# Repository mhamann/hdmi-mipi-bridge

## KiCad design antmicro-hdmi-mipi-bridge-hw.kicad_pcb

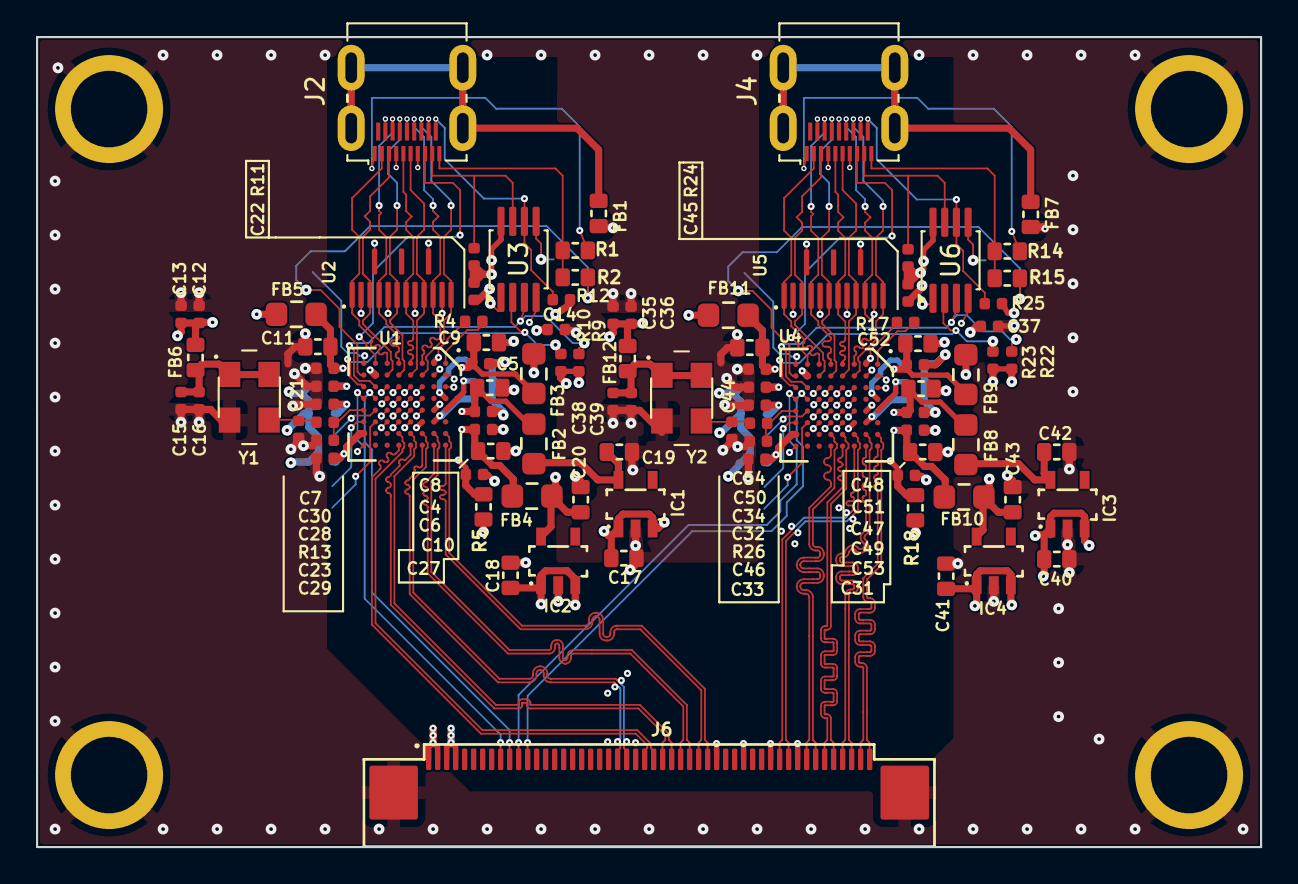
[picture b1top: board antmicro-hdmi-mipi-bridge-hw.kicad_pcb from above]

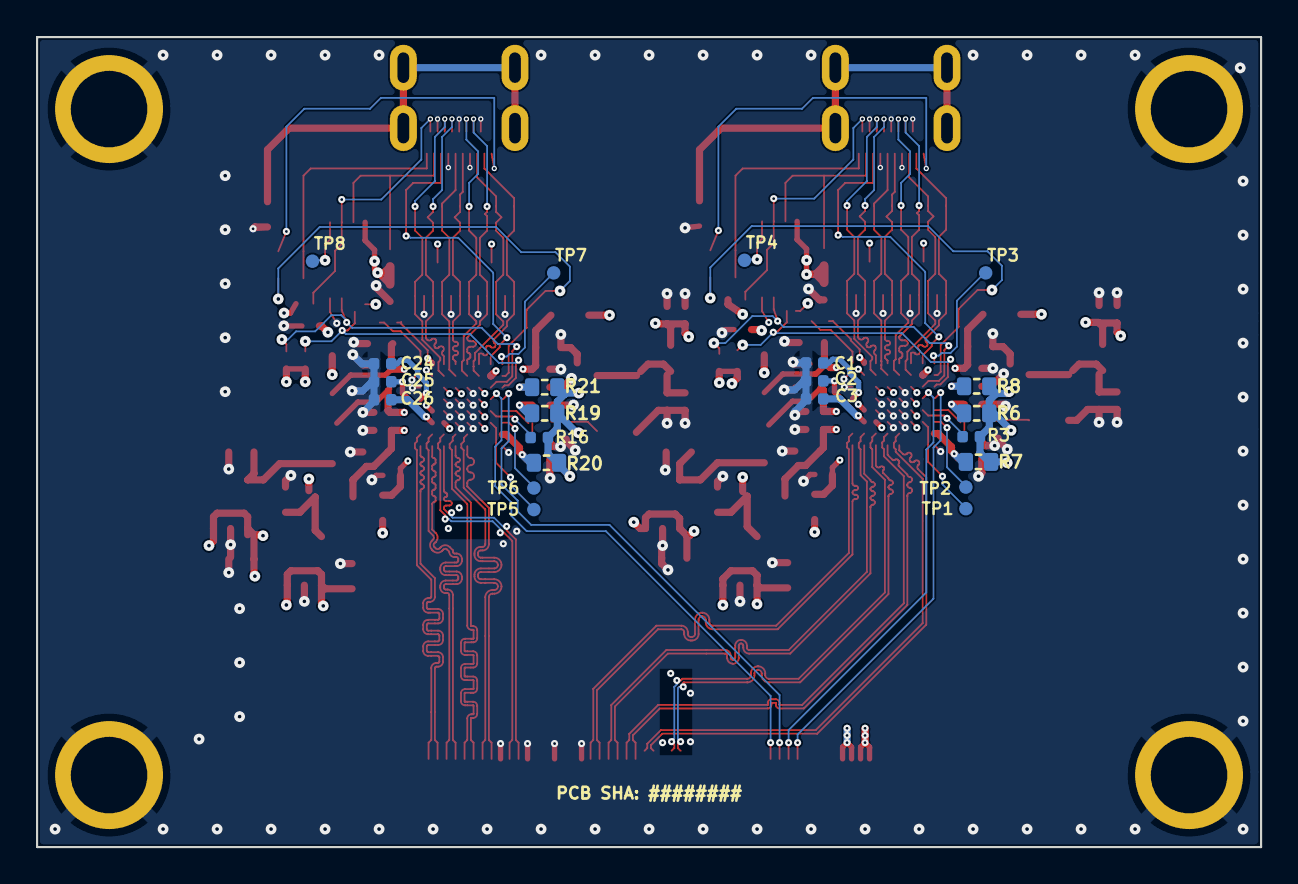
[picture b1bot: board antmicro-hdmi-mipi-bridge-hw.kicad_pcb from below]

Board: 4 copper layers, 68.0 x 45.0 mm, 121 parts (26 on the bottom side), 105 nets.

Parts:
C1, C2, C3, C12, C14, C15, C22, C24, C25, C26, C27, C28, C29, C30, C31, C32, C33, C34, C35, C37, C38, C45: C_100n_0402; C_0402_1005Metric
C4, C5, C6, C7, C47, C48, C49, C50: C_470p_0402; C_0402_1005Metric
C8, C9, C10, C11, C51, C52, C53, C54: C_4u7_0603; C_0603_1608Metric
C13, C16, C21, C23, C36, C39, C44, C46: C_47p_0402; C_0402_1005Metric
C17, C18, C19, C20, C40, C41, C42, C43: C_10u_0603; C_0603_1608Metric
FB1, FB7: FB_120Z_3A_Murata-BLM18SG_0603; FB_0603_1608Metric
FB2, FB3, FB4, FB5, FB8, FB9, FB10, FB11: FB_1kZ_0.8A_WE-CBF_0805; FB_0805_2012Metric
FB6, FB12: FB_600Z_0.5A_Murata-BLM18AG_0603; FB_0603_1608Metric
IC1, IC3: TLV73325PDBVR; SOT-23-5
IC2, IC4: TLV74312PDBVR; SOT-23-5
J2, J4: HDMI-D_Molex_467651001; HDMI_Micro-D_Molex_46765-1xxx
J6: Conn_FFC_WE_68715014022; Conn_FFC_WE_68715014x22
N1: antmicro_logo; antmicro-logo_scaled_20mm_mask
N2: oshw_logo; OSHW-Logo_7.5x8mm_Mask
R1, R2, R5, R6, R7, R8, R14, R15, R18, R19, R20, R21: R_0R_0603; R_0603_1608Metric
R3, R9, R10, R11, R12, R16, R22, R23, R24, R25: R_10k_0402; R_0402_1005Metric
R4, R17: R_2k_0402; R_0402_1005Metric
R13, R26: R_22R_0402; R_0402_1005Metric
SP1, SP2, SP3, SP4: Spacer_Drill4.25mm_H6mm_SMTSO2560CTJ
TP1, TP2, TP3, TP4, TP5, TP6, TP7, TP8: TP_0.75mm_SMD; TP_SMD_0.75mm
U1, U4: TC358743XBG; BGA-64_8x8_6.0x6.0mm
U2, U5: TPD8S009DSMR; R-PDSO-N15
U3, U6: PCA9517ADP; MSOP-8_3x3mm_P0.65mm
Y1, Y2: Oscillator_27MHz_HELE_SSI027000E3CH; Oscillator_SMD_TXC_7C_5x3.2x1.2mm

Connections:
+3V3: C12.2, C13.2, C14.1, C17.2, C18.2, C35.2, C36.2, C37.1, C40.2, C41.2, FB6.1, FB12.1, IC1.1 (VIN), IC1.3 (EN), IC2.1 (VIN), IC2.3 (EN), IC3.1 (VIN), IC3.3 (EN), IC4.1 (VIN), IC4.3 (EN), J6.3, J6.4, R3.2, R6.2, R7.2, R8.2, R9.2, R10.2, R16.2, R19.2, R20.2, R21.2, R22.2, R23.2, U2.13 (VCC), U2.15 (VCC), U3.1, U5.13 (VCC), U5.15 (VCC), U6.1
+5V: C22.2, C45.2, J6.1, J6.2, R11.2, R12.2, R24.2, R25.2, U3.8, U6.8
/Channel 1/CH1_AVDD33: C30.2, R4.2, R8.1, U1.B1 (AVDD33), U1.F3 (AVDD33)
/Channel 1/CH1_REFCLK: C23.2, R13.2, U1.H5 (REFCLK)
/Channel 1/CH1_~RST: R3.1, U1.G5 (~RESET)
/Channel 1/HDMI1_CEC: J2.15, U1.G1 (CEC)
/Channel 1/HDMI1_CLK_N: J2.14, U1.C2 (HDMIC_N), U2.12 (D3-)
/Channel 1/HDMI1_CLK_P: J2.12, U1.C1 (HDMIC_P), U2.10 (D3+)
/Channel 1/HDMI1_D0_N: J2.11, U1.D2 (HDMID0_N), U2.9 (D2-)
/Channel 1/HDMI1_D0_P: J2.9, U1.D1 (HDMID0_P), U2.7 (D2+)
/Channel 1/HDMI1_D1_N: J2.8, U1.E2 (HDMID1_N), U2.6 (D1-)
/Channel 1/HDMI1_D1_P: J2.6, U1.E1 (HDMID1_P), U2.4 (D1+)
/Channel 1/HDMI1_D2_N: J2.5, U1.F2 (HDMID2_N), U2.3 (D0-)
/Channel 1/HDMI1_D2_P: J2.3, U1.F1 (HDMID2_P), U2.1 (D0+)
/Channel 1/HDMI1_DDC_SCL: J2.17, R11.1, U3.7
/Channel 1/HDMI1_DDC_SCL_3V3: R10.1, U1.H3 (DDC_SCL), U3.2
/Channel 1/HDMI1_DDC_SDA: J2.18, R12.1, U3.6
/Channel 1/HDMI1_DDC_SDA_3V3: R9.1, U1.G3 (DDC_SDA), U3.3
/Channel 1/HDMI1_HPD: J2.1, R1.2
/Channel 1/HDMI1_HPDI: R2.2, U1.H2 (HPDI)
/Channel 1/HDMI1_HPDO: TP3.1, U1.H1 (HPDO)
/Channel 1/HDMI1_POWER: J2.19, R1.1, R2.1
/Channel 2/CH2_AVDD33: C34.2, R17.2, R21.1, U4.B1 (AVDD33), U4.F3 (AVDD33)
/Channel 2/CH2_REFCLK: C46.2, R26.2, U4.H5 (REFCLK)
/Channel 2/CH2_~RST: R16.1, U4.G5 (~RESET)
/Channel 2/HDMI2_CEC: J4.15, U4.G1 (CEC)
/Channel 2/HDMI2_CLK_N: J4.14, U4.C2 (HDMIC_N), U5.12 (D3-)
/Channel 2/HDMI2_CLK_P: J4.12, U4.C1 (HDMIC_P), U5.10 (D3+)
/Channel 2/HDMI2_D0_N: J4.11, U4.D2 (HDMID0_N), U5.9 (D2-)
/Channel 2/HDMI2_D0_P: J4.9, U4.D1 (HDMID0_P), U5.7 (D2+)
/Channel 2/HDMI2_D1_N: J4.8, U4.E2 (HDMID1_N), U5.6 (D1-)
/Channel 2/HDMI2_D1_P: J4.6, U4.E1 (HDMID1_P), U5.4 (D1+)
/Channel 2/HDMI2_D2_N: J4.5, U4.F2 (HDMID2_N), U5.3 (D0-)
/Channel 2/HDMI2_D2_P: J4.3, U4.F1 (HDMID2_P), U5.1 (D0+)
/Channel 2/HDMI2_DDC_SCL: J4.17, R24.1, U6.7
/Channel 2/HDMI2_DDC_SCL_3V3: R23.1, U4.H3 (DDC_SCL), U6.2
/Channel 2/HDMI2_DDC_SDA: J4.18, R25.1, U6.6
/Channel 2/HDMI2_DDC_SDA_3V3: R22.1, U4.G3 (DDC_SDA), U6.3
/Channel 2/HDMI2_HPD: J4.1, R14.2
/Channel 2/HDMI2_HPDI: R15.2, U4.H2 (HPDI)
/Channel 2/HDMI2_HPDO: TP7.1, U4.H1 (HPDO)
/Channel 2/HDMI2_POWER: J4.19, R14.1, R15.1
CH1_1V2: C20.2, FB3.2, FB4.2, FB5.2, IC2.5 (VOUT)
CH1_2V5: C19.2, FB2.2, IC1.5 (VOUT)
CH2_1V2: C43.2, FB9.2, FB10.2, FB11.2, IC4.5 (VOUT)
CH2_2V5: C42.2, FB8.2, IC3.5 (VOUT)
CSI1_CLK_N: J6.23, U1.C7 (CSIC_N)
CSI1_CLK_P: J6.22, U1.C8 (CSIC_P)
CSI1_D1_N: J6.26, U1.E7 (CSID0_N)
CSI1_D1_P: J6.25, U1.E8 (CSID0_P)
CSI1_D2_N: J6.28, U1.D7 (CSID1_N)
CSI1_D2_P: J6.27, U1.D8 (CSID1_P)
CSI1_D3_N: J6.30, U1.B7 (CSID2_N)
CSI1_D3_P: J6.29, U1.B8 (CSID2_P)
CSI1_D4_N: J6.32, U1.A7 (CSID3_N)
CSI1_D4_P: J6.31, U1.A8 (CSID3_P)
CSI3_CLK_N: J6.41, U4.C7 (CSIC_N)
CSI3_CLK_P: J6.40, U4.C8 (CSIC_P)
CSI3_D1_N: J6.44, U4.E7 (CSID0_N)
CSI3_D1_P: J6.43, U4.E8 (CSID0_P)
CSI3_D2_N: J6.46, U4.D7 (CSID1_N)
CSI3_D2_P: J6.45, U4.D8 (CSID1_P)
CSI3_D3_N: J6.48, U4.B7 (CSID2_N)
CSI3_D3_P: J6.47, U4.B8 (CSID2_P)
CSI3_D4_N: J6.50, U4.A7 (CSID3_N)
CSI3_D4_P: J6.49, U4.A8 (CSID3_P)
GND: C1.1, C2.1, C3.1, C4.2, C5.2, C6.2, C7.2, C8.1, C9.1, C10.1, C11.1, C12.1, C13.1, C14.2, C15.1, C16.1, C17.1, C18.1, C19.1, C20.1, C21.1, C22.1, C23.1, C24.1, C25.1, C26.1, C27.1, C28.1, C29.1, C30.1, C31.1, C32.1, C33.1, C34.1, C35.1, C36.1, C37.2, C38.1, C39.1, C40.1, C41.1, C42.1, C43.1, C44.1, C45.1, C46.1, C47.2, C48.2, C49.2, C50.2, C51.1, C52.1, C53.1, C54.1, FB1.1, FB7.1, IC1.2 (GND), IC2.2 (GND), IC3.2 (GND), IC4.2 (GND), J2.4, J2.7, J2.10, J2.13, J2.16, J4.4, J4.7, J4.10, J4.13, J4.16, J6.33, J6.36, J6.39, J6.42, J6.MP1 (MP), J6.MP2 (MP), SP1.1, SP2.1, SP3.1, SP4.1, U1.A2 (GND), U1.A3 (VPGM), U1.C4 (GND), U1.C5 (GND), U1.D4 (GND), U1.D5 (GND), U1.D6 (GND), U1.E3 (GND), U1.E4 (GND), U1.E5 (TEST), U1.E6 (GND), U1.H8 (GND), U2.2 (GND), U2.5 (GND), U2.8 (GND), U2.11 (GND), U3.4, U4.A2 (GND), U4.A3 (VPGM), U4.C4 (GND), U4.C5 (GND), U4.D4 (GND), U4.D5 (GND), U4.D6 (GND), U4.E3 (GND), U4.E4 (GND), U4.E5 (TEST), U4.E6 (GND), U4.H8 (GND), U5.2 (GND), U5.5 (GND), U5.8 (GND), U5.11 (GND), U6.4, Y1.2 (GND), Y2.2 (GND)
I2C1_SCL: J6.9, U1.H4 (I2C_SCL)
I2C1_SDA: J6.10, U1.G4 (I2C_SDA)
I2C3_SCL: J6.11, U4.H4 (I2C_SCL)
I2C3_SDA: J6.12, U4.G4 (I2C_SDA)
unnamed: C5.1, C9.2, FB3.1, U1.B2 (AVDD12), U1.D3 (AVDD12)
unnamed: C6.1, C10.2, FB4.1, U1.C6 (VDD_MIPI), U1.F6 (VDD_MIPI)
unnamed: C27.2, R5.1, U1.C3 (VDDC2), U1.F5 (VDDC2)
unnamed: C31.2, R18.1, U4.C3 (VDDC2), U4.F5 (VDDC2)
unnamed: C48.1, C52.2, FB9.1, U4.B2 (AVDD12), U4.D3 (AVDD12)
unnamed: C49.1, C53.2, FB10.1, U4.C6 (VDD_MIPI), U4.F6 (VDD_MIPI)
unnamed: FB1.2, J2.SH
unnamed: FB7.2, J4.SH
unnamed: TP2.1, U1.H6 (EDID_SCL)
unnamed: TP1.1, U1.G6 (EDID_SDA)
unnamed: C4.1, C8.2, FB2.1, U1.B5 (AVDD25)
unnamed: R4.1, U1.A1 (REXT)
unnamed: C7.1, C11.2, FB5.1, R5.2, U1.G2 (VDDC1)
unnamed: C28.2, R6.1, U1.F4 (VDDIO1)
unnamed: C29.2, R7.1, U1.H7 (VDDIO2)
unnamed: C1.2, U1.A4 (BIASDA)
unnamed: C2.2, U1.A5 (DAOUT)
unnamed: C3.2, U1.B6 (PCKIN)
unnamed: TP4.1, U3.5
unnamed: TP6.1, U4.H6 (EDID_SCL)
unnamed: TP5.1, U4.G6 (EDID_SDA)
unnamed: C47.1, C51.2, FB8.1, U4.B5 (AVDD25)
unnamed: R17.1, U4.A1 (REXT)
unnamed: C50.1, C54.2, FB11.1, R18.2, U4.G2 (VDDC1)
unnamed: C32.2, R19.1, U4.F4 (VDDIO1)
unnamed: C33.2, R20.1, U4.H7 (VDDIO2)
unnamed: C24.2, U4.A4 (BIASDA)
unnamed: C25.2, U4.A5 (DAOUT)
unnamed: C26.2, U4.B6 (PCKIN)
unnamed: TP8.1, U6.5
unnamed: C15.2, C16.2, FB6.2, Y1.1 (EN), Y1.4 (VDD)
unnamed: C21.2, R13.1, Y1.3 (OUT)
unnamed: C38.2, C39.2, FB12.2, Y2.1 (EN), Y2.4 (VDD)
unnamed: C44.2, R26.1, Y2.3 (OUT)

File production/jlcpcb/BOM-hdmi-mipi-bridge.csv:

"Comment","Designator","Footprint","LCSC Part #","Qty","Manufacturer","MPN","Ordered part","Notes"
"C_100n_0402","C1,C2,C3,C12,C14,C15,C22,C24,C25,C26,C27,C28,C29,C30,C31,C32,C33,C34,C35,C37,C38,C45","C_0402_1005Metric","C85960","22","Murata","GRM155R61H104KE14D","Murata GRM155R61H104KE14D",""
"C_470p_0402","C4,C5,C6,C7,C47,C48,C49,C50","C_0402_1005Metric","C106207","8","Yageo","CC0402KRX7R9BB471","Yageo CC0402KRX7R9BB471","changed from Walsin 0402B471K250CT (out of stock)"
"C_4u7_0603","C8,C9,C10,C11,C51,C52,C53,C54","C_0603_1608Metric","C329940","8","TDK","C1608X5R1V475KT000E","TDK C1608X5R1V475KT000E","changed from TDK C1608X5R1V475M080AC (out of stock)"
"C_47p_0402","C13,C16,C21,C23,C36,C39,C44,C46","C_0402_1005Metric","C2169042","8","KEMET","C0402C470J5GACTU","KEMET C0402C470J5GACTU",""
"C_10u_0603","C17,C18,C19,C20,C40,C41,C42,C43","C_0603_1608Metric","C77044","8","Murata","GRM188R61A106KE69D","Murata GRM188R61A106KE69D",""
"FB_120Z_3A_Murata-BLM18SG_0603","FB1,FB7","FB_0603_1608Metric","C113030","2","Murata","BLM18SG121TN1D","Murata BLM18SG121TN1D",""
"FB_1kZ_0.8A_WE-CBF_0805","FB2,FB3,FB4,FB5,FB8,FB9,FB10,FB11","FB_0805_2012Metric","C2661448","8","Würth Elektronik","742792096","Wurth 742792096",""
"FB_600Z_0.5A_Murata-BLM18AG_0603","FB6,FB12","FB_0603_1608Metric","C19330","2","Murata","BLM18AG601SN1D","Murata BLM18AG601SN1D",""
"TLV73325PDBVR","IC1,IC3","SOT-23-5","C882825","2","Texas Instruments","TLV73325PDBVR","TI TLV73325PDBVR","reel code of original TLV73325PDBVT"
"TLV74312PDBVR","IC2,IC4","SOT-23-5","C485149","2","Texas Instruments","TLV74312PDBVR","TI TLV74312PDBVR","changed from TLV73312PDBVT (pin-compatible TLV743P, 36 in stock)"
"HDMI-D_Molex_467651001","J2,J4","HDMI_Micro-D_Molex_46765-1xxx","C563878","2","Molex","467651001","Molex 467651001 micro-HDMI","NEW: replaces HDMI-A Molex 471511001"
"Conn_FFC_WE_68715014022","J6","Conn_FFC_WE_68715014x22","C5566958","1","Würth Elektronik","68715014022","Wurth 68715014022","lowest stock on BOM (17)"
"R_0R_0603","R1,R2,R5,R6,R7,R8,R14,R15,R18,R19,R20,R21","R_0603_1608Metric","C512908","12","Bourns","CR0603-J/-000ELF","Bourns CR0603-J/-000ELF",""
"R_10k_0402","R3,R9,R10,R11,R12,R16,R22,R23,R24,R25","R_0402_1005Metric","C202396","10","Bourns","CR0402-FX-1002GLF","Bourns CR0402-FX-1002GLF",""
"R_2k_0402","R4,R17","R_0402_1005Metric","C4109","2","UNI-ROYAL","0402WGF2001TCE","UNI-ROYAL 0402WGF2001TCE","JLC basic; changed from Bourns CR0402-FX-2001GLF"
"R_22R_0402","R13,R26","R_0402_1005Metric","C25092","2","UNI-ROYAL","0402WGF220JTCE","UNI-ROYAL 0402WGF220JTCE","JLC basic; changed from Bourns CR0402-FX-22R0GLF"
"Spacer_Drill4.25mm_H6mm_SMTSO2560CTJ","SP1,SP2,SP3,SP4","Spacer_Drill4.25mm_H6mm_SMTSO2560CTJ","C2916361","4","Sinhoo","SMTSO2560CTJ","Sinhoo SMTSO2560CTJ","changed from Wurth 9774060151R; hole now 4.25 mm"
"TC358743XBG","U1,U4","BGA-64_8x8_6.0x6.0mm","C3008606","2","Toshiba","TC358743XBG","Toshiba TC358743XBG(EL,NOK)","tape&reel ordering code of TC358743XBG"
"TPD8S009DSMR","U2,U5","R-PDSO-N15","C471873","2","Texas Instruments","TPD8S009DSMR","TI TPD8S009DSMR",""
"PCA9517ADP","U3,U6","MSOP-8_3x3mm_P0.65mm","C80799","2","NXP","PCA9517ADP,118","NXP PCA9517ADP,118","changed from PCA9517ATP (HWSON8, 4 in stock); MSOP-8"
"Oscillator_27MHz_HELE_SSI027000E3CH","Y1,Y2","Oscillator_SMD_TXC_7C_5x3.2x1.2mm","C254224","2","HELE (Harmony Electronics)","SSI027000E3CH","HELE SSI027000E3CH","changed from TXC 7C-27.000MBB-T (out of stock)"

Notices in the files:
parts and their libraries:
License: Apache-2.0
